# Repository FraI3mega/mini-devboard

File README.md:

# Mini USB Devboard

<!--toc:start-->
- [Mini USB Devboard](#mini-usb-devboard)
  - [Features](#features)
  - [Schematic](#schematic)
  - [PCB](#pcb)
  - [Case](#case)
  - [Firmware](#firmware)
  - [BOM](#bom)
<!--toc:end-->

A little CH552G USB devboard, for quickly testing ideas.
I wanted a little board, with nice headers for quickly testing modules/ideas, as whenever i need one I can't find one.
That or I don't have the correct cable (shoutout to the RPi Pico's micro usb). It will also be my first time soldering smd, so that will be fun.

## Features

- 2 touch pads
- 2 LEDs
- pinouts for connecting external modules
- pads for I2C pullup resistors

## Schematic

[View in KiCanvas](https://kicanvas.org/?repo=https%3A%2F%2Fgithub.com%2FFraI3mega%2Fmini-devboard%2Ftree%2Fmain%2FPCB)

## PCB

The PCB itself is the USB jack.

## Case

[View in Onshape](https://cad.onshape.com/documents/f293c0d155c2cb71ac8b7631/w/f75f334043fc1f5ab23cc771/e/bf8eef9c1f6021e41664814e?renderMode=0&uiState=6a90c964f0a2f41ef771161a)
 
The PCB is press fit into the case, which adds the necessary thickness for the USB jack.

## Firmware

The included firmware blinks one led, and lights the other one with the touchpad closer to the USB jack.

## BOM

| Name | Qnt | Link | Price |
|-------|-----------|----------   |---------|
|PCB | 5 | jlcpcb.com | 18.70 USD (PCB) + 1.50 USD (Shipping) + 8.92 USD (Taxes) = 29.12 USD |
| OF-SMD2012R Red LED | 2 | [https://www.tme.eu/pl/details/of-smd2012r/diody-led-smd-kolorowe/optoflash/] | 2.78 PLN |
| TSW-105-08-F-D-RA Pins | 1 | [https://www.tme.eu/pl/details/tsw-105-08-f-d-ra/listwy-i-gniazda-kolkowe/samtec/] | 3.96 PLN |
| CH552G | 1 | [https://pl.aliexpress.com/item/1005006904524984.html] | 34.93 (item + taxes) PLN |
| CL10B104KO8NNNL 100nF cap | 3 | [https://www.tme.eu/pl/details/cl10b104ko8nnnl/kondensatory-mlcc-smd/samsung/] | 0.91 PLN |
| WR06X3300FTL 330 Ohm Resistor | 2 | [https://www.tme.eu/pl/details/wr06x3300ftl/rezystory-smd/walsin/] | 0.47 PLN |
| WR06X103JTL 10k Resistor | 1 | [https://www.tme.eu/pl/details/wr06x103jtl/rezystory-smd/walsin/wr06x103-jtl/] | 0.69 PLN |
| TS-1088-AR02016 Switch | 1 | [https://pl.aliexpress.com/item/1005011940516004.html] | 21.31 (item+ taxes) PLN |
| TME Delivery | 1 | - | 17.10 PLN |

Total PLN price: 25.91 (TME) + 34.93 + 21.31 = 82.15 PLN ≈ 23 USD
Total USD: 52.12

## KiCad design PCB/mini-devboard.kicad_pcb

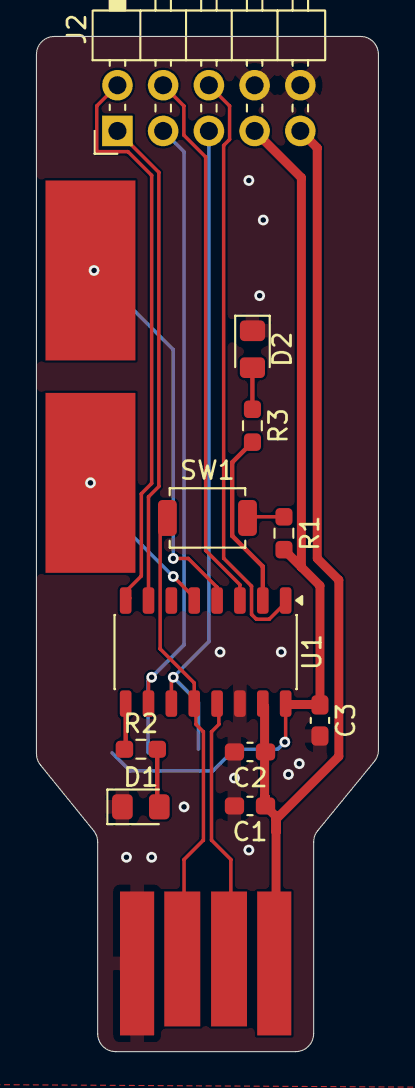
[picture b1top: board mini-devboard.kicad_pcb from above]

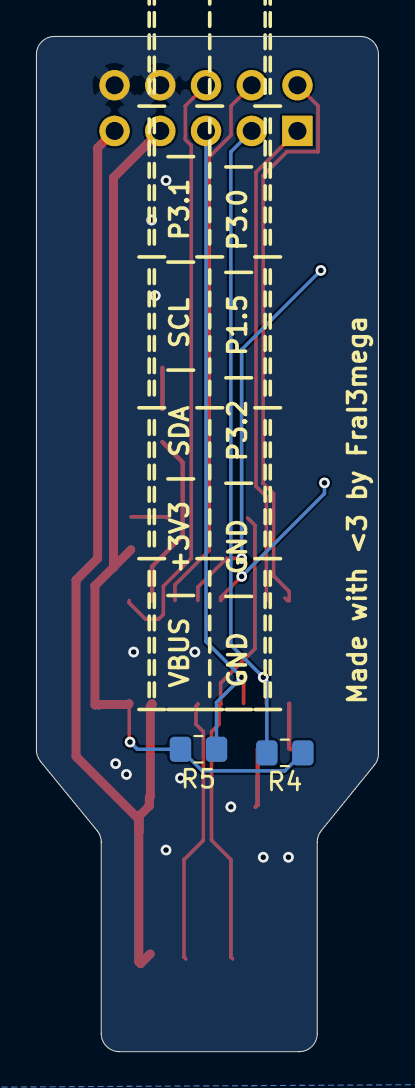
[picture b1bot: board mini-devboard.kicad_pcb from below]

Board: 2 copper layers, 19.0 x 56.4 mm, 16 parts (2 on the bottom side), 18 nets.

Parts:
C1, C2, C3: 100nF; C_0603_1608Metric_Pad1.08x0.95mm_HandSolder
D1, D2: LED; LED_0805_2012Metric_Pad1.15x1.40mm_HandSolder
J1: USB_A; USB-A
J2: Conn_02x05_Counter_Clockwise; PinHeader_2x05_P2.54mm_Horizontal
R1: 10k; R_0603_1608Metric_Pad0.98x0.95mm_HandSolder
R2, R3: 330; R_0603_1608Metric_Pad0.98x0.95mm_HandSolder
R4, R5: ?; R_0805_2012Metric_Pad1.20x1.40mm_HandSolder
SW1: SW_Push; SW_SPST_TS-1088-xR020
TP1, TP2: TestPoint_Alt; TestPoint_Pad_4.0x4.0mm
U1: CH552G; JEITA_SOIC-16_3.9x9.9mm_P1.27mm

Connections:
+3V3: C3.1, J2.7, R1.2, R4.2, R5.2, U1.16 (3V3)
/LED1: R2.1, U1.9 (P1.1)
/LED2: R3.2, U1.2 (P1.4)
/P1.5: J2.4, U1.3 (P1.5)
/P3.0: J2.2, U1.8 (P3.0)
/P3.1: J2.1, U1.7 (P3.1)
/P3.2: J2.6, U1.1 (P3.2)
/Touch1: TP1.1 (1_1), U1.5 (P1.7)
/Touch2: TP2.1 (1_1), U1.4 (P1.6)
D+: J1.3 (D+), SW1.1, U1.12 (P3.6)
D-: J1.2 (D-), U1.13 (P3.7)
GND: C1.2, C2.2, C3.2, D1.1 (K), D2.1 (K), J1.4 (GND), J2.8, J2.10, U1.14 (GND)
unnamed: D1.2 (A), R2.2
unnamed: D2.2 (A), R3.1
unnamed: R1.1, SW1.2
SCL: J2.3, R4.1, U1.10 (P3.3)
SDA: J2.5, R5.1, U1.11 (P3.4)
VBUS: C1.1, C2.1, J1.1 (VBUS), J2.9, U1.15 (VCC)
